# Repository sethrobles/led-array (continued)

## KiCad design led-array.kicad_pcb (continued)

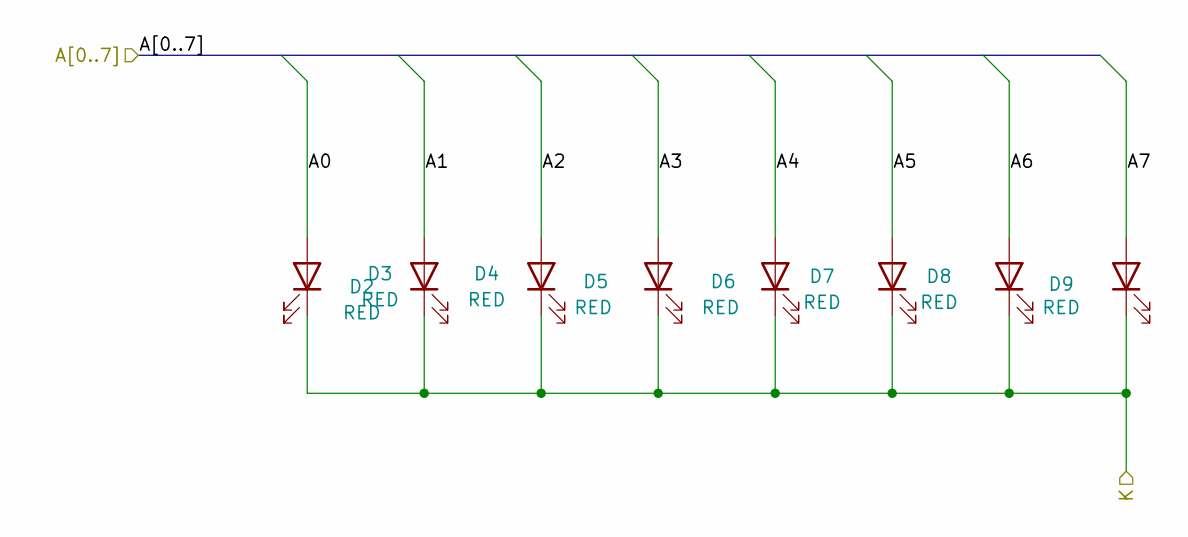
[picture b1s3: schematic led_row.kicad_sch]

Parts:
D2, D3, D4, D5, D6, D7, D8, D9: RED; LED_0603_1608Metric; LCSC C2286

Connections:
/LED Group 0/Led Module 1/A0: D2.2 (A); also elsewhere on the board
/LED Group 0/Led Module 1/A1: D3.2 (A); also elsewhere on the board
/LED Group 0/Led Module 1/A2: D4.2 (A); also elsewhere on the board
/LED Group 0/Led Module 1/A3: D5.2 (A); also elsewhere on the board
/LED Group 0/Led Module 1/A4: D6.2 (A); also elsewhere on the board
/LED Group 0/Led Module 1/A5: D7.2 (A); also elsewhere on the board
/LED Group 0/Led Module 1/A6: D8.2 (A); also elsewhere on the board
/LED Group 0/Led Module 1/A7: D9.2 (A); also elsewhere on the board
K5: D2.1 (K), D3.1 (K), D4.1 (K), D5.1 (K), D6.1 (K), D7.1 (K), D8.1 (K), D9.1 (K); also elsewhere on the board

Parts of its further copies:
D10, D11, D12, D13, D14, D15, D16, D17, D18, D19, D20, D21, D22, D23, D24, D25, D26, D27, D28, D29, D30, D31, D32, D33, D34, D35, D36, D37, D38, D39, D40, D41, D42, D43, D44, D45, D46, D47, D48, D49, D50, D51, D52, D53, D54, D55, D56, D57, D58, D59, D60, D61, D62, D63, D64, D65, D66, D67, D68, D69, D70, D71, D72, D73, D74, D75, D76, D77, D78, D79, D80, D81, D82, D83, D84, D85, D86, D87, D88, D89, D90, D91, D92, D93, D94, D95, D96, D97, D98, D99, D100, D101, D102, D103, D104, D105, D106, D107, D108, D109, D110, D111, D112, D113, D114, D115, D116, D117, D118, D119, D120, D121, D122, D123, D124, D125, D126, D127, D128, D129, D130, D131, D132, D133, D134, D135, D136, D137, D138, D139, D140, D141, D142, D143, D144, D145, D146, D147, D148, D149, D150, D151, D152, D153, D154, D155, D156, D157, D158, D159, D160, D161, D162, D163, D164, D165, D166, D167, D168, D169, D170, D171, D172, D173, D174, D175, D176, D177, D178, D179, D180, D181, D182, D183, D184, D185, D186, D187, D188, D189, D190, D191, D192, D193, D194, D195, D196, D197, D198, D199, D200, D201, D202, D203, D204, D205, D206, D207, D208, D209, D210, D211, D212, D213, D214, D215, D216, D217, D218, D219, D220, D221, D222, D223, D224, D225, D226, D227, D228, D229, D230, D231, D232, D233, D234, D235, D236, D237, D238, D239, D240, D241, D242, D243, D244, D245, D246, D247, D248, D249, D250, D251, D252, D253, D254, D255, D256, D257, D258, D259, D260, D261, D262, D263, D264, D265, D266, D267, D268, D269, D270, D271, D272, D273, D274, D275, D276, D277, D278, D279, D280, D281, D282, D283, D284, D285, D286, D287, D288, D289, D290, D291, D292, D293, D294, D295, D296, D297, D298, D299, D300, D301, D302, D303, D304, D305, D306, D307, D308, D309, D310, D311, D312, D313, D314, D315, D316, D317, D318, D319, D320, D321, D322, D323, D324, D325, D326, D327, D328, D329, D330, D331, D332, D333, D334, D335, D336, D337, D338, D339, D340, D341, D342, D343, D344, D345, D346, D347, D348, D349, D350, D351, D352, D353, D354, D355, D356, D357, D358, D359, D360, D361, D362, D363, D364, D365, D366, D367, D368, D369, D370, D371, D372, D373, D374, D375, D376, D377, D378, D379, D380, D381, D382, D383, D384, D385, D386, D387, D388, D389, D390, D391, D392, D393, D394, D395, D396, D397, D398, D399, D400, D401, D402, D403, D404, D405, D406, D407, D408, D409, D410, D411, D412, D413, D414, D415, D416, D417, D418, D419, D420, D421, D422, D423, D424, D425, D426, D427, D428, D429, D430, D431, D432, D433, D434, D435, D436, D437, D438, D439, D440, D441, D442, D443, D444, D445, D446, D447, D448, D449, D450, D451, D452, D453, D454, D455, D456, D457, D458, D459, D460, D461, D462, D463, D464, D465, D466, D467, D468, D469, D470, D471, D472, D473, D474, D475, D476, D477, D478, D479, D480, D481, D482, D483, D484, D485, D486, D487, D488, D489, D490, D491, D492, D493, D494, D495, D496, D497, D498, D499, D500, D501, D502, D503, D504, D505, D506, D507, D508, D509, D510, D511, D512, D513, D514, D515, D516, D517, D518, D519, D520, D521, D522, D523, D524, D525, D526, D527, D528, D529, D530, D531, D532, D533, D534, D535, D536, D537, D538, D539, D540, D541, D542, D543, D544, D545, D546, D547, D548, D549, D550, D551, D552, D553, D554, D555, D556, D557, D558, D559, D560, D561, D562, D563, D564, D565, D566, D567, D568, D569, D570, D571, D572, D573, D574, D575, D576, D577, D578, D579, D580, D581, D582, D583, D584, D585, D586, D587, D588, D589, D590, D591, D592, D593, D594, D595, D596, D597, D598, D599, D600, D601, D602, D603, D604, D605, D606, D607, D608, D609, D610, D611, D612, D613, D614, D615, D616, D617, D618, D619, D620, D621, D622, D623, D624, D625, D626, D627, D628, D629, D630, D631, D632, D633, D634, D635, D636, D637, D638, D639, D640, D641, D642, D643, D644, D645, D646, D647, D648, D649, D650, D651, D652, D653, D654, D655, D656, D657, D658, D659, D660, D661, D662, D663, D664, D665, D666, D667, D668, D669, D670, D671, D672, D673, D674, D675, D676, D677, D678, D679, D680, D681, D682, D683, D684, D685, D686, D687, D688, D689, D690, D691, D692, D693, D694, D695, D696, D697, D698, D699, D700, D701, D702, D703, D704, D705, D706, D707, D708, D709, D710, D711, D712, D713, D714, D715, D716, D717, D718, D719, D720, D721, D722, D723, D724, D725, D726, D727, D728, D729, D730, D731, D732, D733, D734, D735, D736, D737, D738, D739, D740, D741, D742, D743, D744, D745, D746, D747, D748, D749, D750, D751, D752, D753, D754, D755, D756, D757, D758, D759, D760, D761, D762, D763, D764, D765, D766, D767, D768, D769, D770, D771, D772, D773, D774, D775, D776, D777, D778, D779, D780, D781, D782, D783, D784, D785, D786, D787, D788, D789, D790, D791, D792, D793, D794, D795, D796, D797, D798, D799, D800, D801, D802, D803, D804, D805, D806, D807, D808, D809, D810, D811, D812, D813, D814, D815, D816, D817, D818, D819, D820, D821, D822, D823, D824, D825, D826, D827, D828, D829, D830, D831, D832, D833, D834, D835, D836, D837, D838, D839, D840, D841, D842, D843, D844, D845, D846, D847, D848, D849, D850, D851, D852, D853, D854, D855, D856, D857, D858, D859, D860, D861, D862, D863, D864, D865, D866, D867, D868, D869, D870, D871, D872, D873, D874, D875, D876, D877, D878, D879, D880, D881, D882, D883, D884, D885, D886, D887, D888, D889, D890, D891, D892, D893, D894, D895, D896, D897, D898, D899, D900, D901, D902, D903, D904, D905, D906, D907, D908, D909, D910, D911, D912, D913, D914, D915, D916, D917, D918, D919, D920, D921, D922, D923, D924, D925, D926, D927, D928, D929, D930, D931, D932, D933, D934, D935, D936, D937, D938, D939, D940, D941, D942, D943, D944, D945, D946, D947, D948, D949, D950, D951, D952, D953, D954, D955, D956, D957, D958, D959, D960, D961, D962, D963, D964, D965, D966, D967, D968, D969, D970, D971, D972, D973, D974, D975, D976, D977, D978, D979, D980, D981, D982, D983, D984, D985, D986, D987, D988, D989, D990, D991, D992, D993, D994, D995, D996, D997, D998, D999, D1000, D1001, D1002, D1003, D1004, D1005, D1006, D1007, D1008, D1009, D1010, D1011, D1012, D1013, D1014, D1015, D1016, D1017, D1018, D1019, D1020, D1021, D1022, D1023, D1024, D1025: RED; LED_0603_1608Metric; LCSC C2286

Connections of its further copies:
/LED Group 0/Led Module 1/A0: D10.2 (A), D18.2 (A), D26.2 (A), D34.2 (A), D42.2 (A), D50.2 (A), D58.2 (A); also elsewhere on the board
/LED Group 0/Led Module 1/A1: D11.2 (A), D19.2 (A), D27.2 (A), D35.2 (A), D43.2 (A), D51.2 (A), D59.2 (A); also elsewhere on the board
/LED Group 0/Led Module 1/A2: D12.2 (A), D20.2 (A), D28.2 (A), D36.2 (A), D44.2 (A), D52.2 (A), D60.2 (A); also elsewhere on the board
/LED Group 0/Led Module 1/A3: D13.2 (A), D21.2 (A), D29.2 (A), D37.2 (A), D45.2 (A), D53.2 (A), D61.2 (A); also elsewhere on the board
/LED Group 0/Led Module 1/A4: D14.2 (A), D22.2 (A), D30.2 (A), D38.2 (A), D46.2 (A), D54.2 (A), D62.2 (A); also elsewhere on the board
/LED Group 0/Led Module 1/A5: D15.2 (A), D23.2 (A), D31.2 (A), D39.2 (A), D47.2 (A), D55.2 (A), D63.2 (A); also elsewhere on the board
/LED Group 0/Led Module 1/A6: D16.2 (A), D24.2 (A), D32.2 (A), D40.2 (A), D48.2 (A), D56.2 (A), D64.2 (A); also elsewhere on the board
/LED Group 0/Led Module 1/A7: D17.2 (A), D25.2 (A), D33.2 (A), D41.2 (A), D49.2 (A), D57.2 (A), D65.2 (A); also elsewhere on the board
/LED Group 0/Led Module 2/A0: D66.2 (A), D74.2 (A), D82.2 (A), D90.2 (A), D98.2 (A), D106.2 (A), D114.2 (A), D122.2 (A); also elsewhere on the board
/LED Group 0/Led Module 2/A1: D67.2 (A), D75.2 (A), D83.2 (A), D91.2 (A), D99.2 (A), D107.2 (A), D115.2 (A), D123.2 (A); also elsewhere on the board
/LED Group 0/Led Module 2/A2: D68.2 (A), D76.2 (A), D84.2 (A), D92.2 (A), D100.2 (A), D108.2 (A), D116.2 (A), D124.2 (A); also elsewhere on the board
/LED Group 0/Led Module 2/A3: D69.2 (A), D77.2 (A), D85.2 (A), D93.2 (A), D101.2 (A), D109.2 (A), D117.2 (A), D125.2 (A); also elsewhere on the board
/LED Group 0/Led Module 2/A4: D70.2 (A), D78.2 (A), D86.2 (A), D94.2 (A), D102.2 (A), D110.2 (A), D118.2 (A), D126.2 (A); also elsewhere on the board
/LED Group 0/Led Module 2/A5: D71.2 (A), D79.2 (A), D87.2 (A), D95.2 (A), D103.2 (A), D111.2 (A), D119.2 (A), D127.2 (A); also elsewhere on the board
/LED Group 0/Led Module 2/A6: D72.2 (A), D80.2 (A), D88.2 (A), D96.2 (A), D104.2 (A), D112.2 (A), D120.2 (A), D128.2 (A); also elsewhere on the board
/LED Group 0/Led Module 2/A7: D73.2 (A), D81.2 (A), D89.2 (A), D97.2 (A), D105.2 (A), D113.2 (A), D121.2 (A), D129.2 (A); also elsewhere on the board
/LED Group 0/Led Module 3/A0: D130.2 (A), D138.2 (A), D146.2 (A), D154.2 (A), D162.2 (A), D170.2 (A), D218.2 (A), D226.2 (A); also elsewhere on the board
/LED Group 0/Led Module 3/A1: D131.2 (A), D139.2 (A), D147.2 (A), D155.2 (A), D163.2 (A), D171.2 (A), D219.2 (A), D227.2 (A); also elsewhere on the board
/LED Group 0/Led Module 3/A2: D132.2 (A), D140.2 (A), D148.2 (A), D156.2 (A), D164.2 (A), D172.2 (A), D220.2 (A), D228.2 (A); also elsewhere on the board
/LED Group 0/Led Module 3/A3: D133.2 (A), D141.2 (A), D149.2 (A), D157.2 (A), D165.2 (A), D173.2 (A), D221.2 (A), D229.2 (A); also elsewhere on the board
/LED Group 0/Led Module 3/A4: D134.2 (A), D142.2 (A), D150.2 (A), D158.2 (A), D166.2 (A), D174.2 (A), D222.2 (A), D230.2 (A); also elsewhere on the board
/LED Group 0/Led Module 3/A5: D135.2 (A), D143.2 (A), D151.2 (A), D159.2 (A), D167.2 (A), D175.2 (A), D223.2 (A), D231.2 (A); also elsewhere on the board
/LED Group 0/Led Module 3/A6: D136.2 (A), D144.2 (A), D152.2 (A), D160.2 (A), D168.2 (A), D176.2 (A), D224.2 (A), D232.2 (A); also elsewhere on the board
/LED Group 0/Led Module 3/A7: D137.2 (A), D145.2 (A), D153.2 (A), D161.2 (A), D169.2 (A), D177.2 (A), D225.2 (A), D233.2 (A); also elsewhere on the board
/LED Group 0/Led Module 4/A0: D274.2 (A), D282.2 (A), D338.2 (A), D346.2 (A), D394.2 (A), D402.2 (A), D450.2 (A), D458.2 (A); also elsewhere on the board
/LED Group 0/Led Module 4/A1: D275.2 (A), D283.2 (A), D339.2 (A), D347.2 (A), D395.2 (A), D403.2 (A), D451.2 (A), D459.2 (A); also elsewhere on the board
/LED Group 0/Led Module 4/A2: D276.2 (A), D284.2 (A), D340.2 (A), D348.2 (A), D396.2 (A), D404.2 (A), D452.2 (A), D460.2 (A); also elsewhere on the board
/LED Group 0/Led Module 4/A3: D277.2 (A), D285.2 (A), D341.2 (A), D349.2 (A), D397.2 (A), D405.2 (A), D453.2 (A), D461.2 (A); also elsewhere on the board
/LED Group 0/Led Module 4/A4: D278.2 (A), D286.2 (A), D342.2 (A), D350.2 (A), D398.2 (A), D406.2 (A), D454.2 (A), D462.2 (A); also elsewhere on the board
/LED Group 0/Led Module 4/A5: D279.2 (A), D287.2 (A), D343.2 (A), D351.2 (A), D399.2 (A), D407.2 (A), D455.2 (A), D463.2 (A); also elsewhere on the board
/LED Group 0/Led Module 4/A6: D280.2 (A), D288.2 (A), D344.2 (A), D352.2 (A), D400.2 (A), D408.2 (A), D456.2 (A), D464.2 (A); also elsewhere on the board
/LED Group 0/Led Module 4/A7: D281.2 (A), D289.2 (A), D345.2 (A), D353.2 (A), D401.2 (A), D409.2 (A), D457.2 (A), D465.2 (A); also elsewhere on the board
/LED Group 1/Led Module 1/A0: D258.2 (A), D266.2 (A), D290.2 (A), D298.2 (A), D306.2 (A), D314.2 (A), D322.2 (A), D330.2 (A); also elsewhere on the board
/LED Group 1/Led Module 1/A1: D259.2 (A), D267.2 (A), D291.2 (A), D299.2 (A), D307.2 (A), D315.2 (A), D323.2 (A), D331.2 (A); also elsewhere on the board
/LED Group 1/Led Module 1/A2: D260.2 (A), D268.2 (A), D292.2 (A), D300.2 (A), D308.2 (A), D316.2 (A), D324.2 (A), D332.2 (A); also elsewhere on the board
/LED Group 1/Led Module 1/A3: D261.2 (A), D269.2 (A), D293.2 (A), D301.2 (A), D309.2 (A), D317.2 (A), D325.2 (A), D333.2 (A); also elsewhere on the board
/LED Group 1/Led Module 1/A4: D262.2 (A), D270.2 (A), D294.2 (A), D302.2 (A), D310.2 (A), D318.2 (A), D326.2 (A), D334.2 (A); also elsewhere on the board
/LED Group 1/Led Module 1/A5: D263.2 (A), D271.2 (A), D295.2 (A), D303.2 (A), D311.2 (A), D319.2 (A), D327.2 (A), D335.2 (A); also elsewhere on the board
/LED Group 1/Led Module 1/A6: D264.2 (A), D272.2 (A), D296.2 (A), D304.2 (A), D312.2 (A), D320.2 (A), D328.2 (A), D336.2 (A); also elsewhere on the board
/LED Group 1/Led Module 1/A7: D265.2 (A), D273.2 (A), D297.2 (A), D305.2 (A), D313.2 (A), D321.2 (A), D329.2 (A), D337.2 (A); also elsewhere on the board
/LED Group 1/Led Module 2/A0: D178.2 (A), D186.2 (A), D194.2 (A), D202.2 (A), D210.2 (A), D234.2 (A), D242.2 (A), D250.2 (A); also elsewhere on the board
/LED Group 1/Led Module 2/A1: D179.2 (A), D187.2 (A), D195.2 (A), D203.2 (A), D211.2 (A), D235.2 (A), D243.2 (A), D251.2 (A); also elsewhere on the board
/LED Group 1/Led Module 2/A2: D180.2 (A), D188.2 (A), D196.2 (A), D204.2 (A), D212.2 (A), D236.2 (A), D244.2 (A), D252.2 (A); also elsewhere on the board
/LED Group 1/Led Module 2/A3: D181.2 (A), D189.2 (A), D197.2 (A), D205.2 (A), D213.2 (A), D237.2 (A), D245.2 (A), D253.2 (A); also elsewhere on the board
/LED Group 1/Led Module 2/A4: D182.2 (A), D190.2 (A), D198.2 (A), D206.2 (A), D214.2 (A), D238.2 (A), D246.2 (A), D254.2 (A); also elsewhere on the board
/LED Group 1/Led Module 2/A5: D183.2 (A), D191.2 (A), D199.2 (A), D207.2 (A), D215.2 (A), D239.2 (A), D247.2 (A), D255.2 (A); also elsewhere on the board
/LED Group 1/Led Module 2/A6: D184.2 (A), D192.2 (A), D200.2 (A), D208.2 (A), D216.2 (A), D240.2 (A), D248.2 (A), D256.2 (A); also elsewhere on the board
/LED Group 1/Led Module 2/A7: D185.2 (A), D193.2 (A), D201.2 (A), D209.2 (A), D217.2 (A), D241.2 (A), D249.2 (A), D257.2 (A); also elsewhere on the board
/LED Group 1/Led Module 3/A0: D354.2 (A), D362.2 (A), D370.2 (A), D378.2 (A), D386.2 (A), D410.2 (A), D418.2 (A), D426.2 (A); also elsewhere on the board
/LED Group 1/Led Module 3/A1: D355.2 (A), D363.2 (A), D371.2 (A), D379.2 (A), D387.2 (A), D411.2 (A), D419.2 (A), D427.2 (A); also elsewhere on the board
/LED Group 1/Led Module 3/A2: D356.2 (A), D364.2 (A), D372.2 (A), D380.2 (A), D388.2 (A), D412.2 (A), D420.2 (A), D428.2 (A); also elsewhere on the board
/LED Group 1/Led Module 3/A3: D357.2 (A), D365.2 (A), D373.2 (A), D381.2 (A), D389.2 (A), D413.2 (A), D421.2 (A), D429.2 (A); also elsewhere on the board
/LED Group 1/Led Module 3/A4: D358.2 (A), D366.2 (A), D374.2 (A), D382.2 (A), D390.2 (A), D414.2 (A), D422.2 (A), D430.2 (A); also elsewhere on the board
/LED Group 1/Led Module 3/A5: D359.2 (A), D367.2 (A), D375.2 (A), D383.2 (A), D391.2 (A), D415.2 (A), D423.2 (A), D431.2 (A); also elsewhere on the board
/LED Group 1/Led Module 3/A6: D360.2 (A), D368.2 (A), D376.2 (A), D384.2 (A), D392.2 (A), D416.2 (A), D424.2 (A), D432.2 (A); also elsewhere on the board
/LED Group 1/Led Module 3/A7: D361.2 (A), D369.2 (A), D377.2 (A), D385.2 (A), D393.2 (A), D417.2 (A), D425.2 (A), D433.2 (A); also elsewhere on the board
/LED Group 1/Led Module 4/A0: D434.2 (A), D442.2 (A), D466.2 (A), D474.2 (A), D482.2 (A), D490.2 (A), D498.2 (A), D506.2 (A); also elsewhere on the board
/LED Group 1/Led Module 4/A1: D435.2 (A), D443.2 (A), D467.2 (A), D475.2 (A), D483.2 (A), D491.2 (A), D499.2 (A), D507.2 (A); also elsewhere on the board
/LED Group 1/Led Module 4/A2: D436.2 (A), D444.2 (A), D468.2 (A), D476.2 (A), D484.2 (A), D492.2 (A), D500.2 (A), D508.2 (A); also elsewhere on the board
/LED Group 1/Led Module 4/A3: D437.2 (A), D445.2 (A), D469.2 (A), D477.2 (A), D485.2 (A), D493.2 (A), D501.2 (A), D509.2 (A); also elsewhere on the board
/LED Group 1/Led Module 4/A4: D438.2 (A), D446.2 (A), D470.2 (A), D478.2 (A), D486.2 (A), D494.2 (A), D502.2 (A), D510.2 (A); also elsewhere on the board
/LED Group 1/Led Module 4/A5: D439.2 (A), D447.2 (A), D471.2 (A), D479.2 (A), D487.2 (A), D495.2 (A), D503.2 (A), D511.2 (A); also elsewhere on the board
/LED Group 1/Led Module 4/A6: D440.2 (A), D448.2 (A), D472.2 (A), D480.2 (A), D488.2 (A), D496.2 (A), D504.2 (A), D512.2 (A); also elsewhere on the board
/LED Group 1/Led Module 4/A7: D441.2 (A), D449.2 (A), D473.2 (A), D481.2 (A), D489.2 (A), D497.2 (A), D505.2 (A), D513.2 (A); also elsewhere on the board
/LED Group 2/Led Module 1/A0: D578.2 (A), D586.2 (A), D594.2 (A), D602.2 (A), D610.2 (A), D618.2 (A), D626.2 (A), D634.2 (A); also elsewhere on the board
/LED Group 2/Led Module 1/A1: D579.2 (A), D587.2 (A), D595.2 (A), D603.2 (A), D611.2 (A), D619.2 (A), D627.2 (A), D635.2 (A); also elsewhere on the board
/LED Group 2/Led Module 1/A2: D580.2 (A), D588.2 (A), D596.2 (A), D604.2 (A), D612.2 (A), D620.2 (A), D628.2 (A), D636.2 (A); also elsewhere on the board
/LED Group 2/Led Module 1/A3: D581.2 (A), D589.2 (A), D597.2 (A), D605.2 (A), D613.2 (A), D621.2 (A), D629.2 (A), D637.2 (A); also elsewhere on the board
/LED Group 2/Led Module 1/A4: D582.2 (A), D590.2 (A), D598.2 (A), D606.2 (A), D614.2 (A), D622.2 (A), D630.2 (A), D638.2 (A); also elsewhere on the board
/LED Group 2/Led Module 1/A5: D583.2 (A), D591.2 (A), D599.2 (A), D607.2 (A), D615.2 (A), D623.2 (A), D631.2 (A), D639.2 (A); also elsewhere on the board
/LED Group 2/Led Module 1/A6: D584.2 (A), D592.2 (A), D600.2 (A), D608.2 (A), D616.2 (A), D624.2 (A), D632.2 (A), D640.2 (A); also elsewhere on the board
/LED Group 2/Led Module 1/A7: D585.2 (A), D593.2 (A), D601.2 (A), D609.2 (A), D617.2 (A), D625.2 (A), D633.2 (A), D641.2 (A); also elsewhere on the board
/LED Group 2/Led Module 2/A0: D514.2 (A), D522.2 (A), D530.2 (A), D538.2 (A), D546.2 (A), D554.2 (A), D562.2 (A), D570.2 (A); also elsewhere on the board
/LED Group 2/Led Module 2/A1: D515.2 (A), D523.2 (A), D531.2 (A), D539.2 (A), D547.2 (A), D555.2 (A), D563.2 (A), D571.2 (A); also elsewhere on the board
/LED Group 2/Led Module 2/A2: D516.2 (A), D524.2 (A), D532.2 (A), D540.2 (A), D548.2 (A), D556.2 (A), D564.2 (A), D572.2 (A); also elsewhere on the board
/LED Group 2/Led Module 2/A3: D517.2 (A), D525.2 (A), D533.2 (A), D541.2 (A), D549.2 (A), D557.2 (A), D565.2 (A), D573.2 (A); also elsewhere on the board
/LED Group 2/Led Module 2/A4: D518.2 (A), D526.2 (A), D534.2 (A), D542.2 (A), D550.2 (A), D558.2 (A), D566.2 (A), D574.2 (A); also elsewhere on the board
/LED Group 2/Led Module 2/A5: D519.2 (A), D527.2 (A), D535.2 (A), D543.2 (A), D551.2 (A), D559.2 (A), D567.2 (A), D575.2 (A); also elsewhere on the board
/LED Group 2/Led Module 2/A6: D520.2 (A), D528.2 (A), D536.2 (A), D544.2 (A), D552.2 (A), D560.2 (A), D568.2 (A), D576.2 (A); also elsewhere on the board
/LED Group 2/Led Module 2/A7: D521.2 (A), D529.2 (A), D537.2 (A), D545.2 (A), D553.2 (A), D561.2 (A), D569.2 (A), D577.2 (A); also elsewhere on the board
/LED Group 2/Led Module 3/A0: D642.2 (A), D650.2 (A), D658.2 (A), D666.2 (A), D674.2 (A), D682.2 (A), D690.2 (A), D698.2 (A); also elsewhere on the board
/LED Group 2/Led Module 3/A1: D643.2 (A), D651.2 (A), D659.2 (A), D667.2 (A), D675.2 (A), D683.2 (A), D691.2 (A), D699.2 (A); also elsewhere on the board
/LED Group 2/Led Module 3/A2: D644.2 (A), D652.2 (A), D660.2 (A), D668.2 (A), D676.2 (A), D684.2 (A), D692.2 (A), D700.2 (A); also elsewhere on the board
/LED Group 2/Led Module 3/A3: D645.2 (A), D653.2 (A), D661.2 (A), D669.2 (A), D677.2 (A), D685.2 (A), D693.2 (A), D701.2 (A); also elsewhere on the board
/LED Group 2/Led Module 3/A4: D646.2 (A), D654.2 (A), D662.2 (A), D670.2 (A), D678.2 (A), D686.2 (A), D694.2 (A), D702.2 (A); also elsewhere on the board
/LED Group 2/Led Module 3/A5: D647.2 (A), D655.2 (A), D663.2 (A), D671.2 (A), D679.2 (A), D687.2 (A), D695.2 (A), D703.2 (A); also elsewhere on the board
/LED Group 2/Led Module 3/A6: D648.2 (A), D656.2 (A), D664.2 (A), D672.2 (A), D680.2 (A), D688.2 (A), D696.2 (A), D704.2 (A); also elsewhere on the board
/LED Group 2/Led Module 3/A7: D649.2 (A), D657.2 (A), D665.2 (A), D673.2 (A), D681.2 (A), D689.2 (A), D697.2 (A), D705.2 (A); also elsewhere on the board
/LED Group 2/Led Module 4/A0: D706.2 (A), D714.2 (A), D722.2 (A), D730.2 (A), D738.2 (A), D746.2 (A), D754.2 (A), D762.2 (A); also elsewhere on the board
/LED Group 2/Led Module 4/A1: D707.2 (A), D715.2 (A), D723.2 (A), D731.2 (A), D739.2 (A), D747.2 (A), D755.2 (A), D763.2 (A); also elsewhere on the board
/LED Group 2/Led Module 4/A2: D708.2 (A), D716.2 (A), D724.2 (A), D732.2 (A), D740.2 (A), D748.2 (A), D756.2 (A), D764.2 (A); also elsewhere on the board
/LED Group 2/Led Module 4/A3: D709.2 (A), D717.2 (A), D725.2 (A), D733.2 (A), D741.2 (A), D749.2 (A), D757.2 (A), D765.2 (A); also elsewhere on the board
/LED Group 2/Led Module 4/A4: D710.2 (A), D718.2 (A), D726.2 (A), D734.2 (A), D742.2 (A), D750.2 (A), D758.2 (A), D766.2 (A); also elsewhere on the board
/LED Group 2/Led Module 4/A5: D711.2 (A), D719.2 (A), D727.2 (A), D735.2 (A), D743.2 (A), D751.2 (A), D759.2 (A), D767.2 (A); also elsewhere on the board
/LED Group 2/Led Module 4/A6: D712.2 (A), D720.2 (A), D728.2 (A), D736.2 (A), D744.2 (A), D752.2 (A), D760.2 (A), D768.2 (A); also elsewhere on the board
/LED Group 2/Led Module 4/A7: D713.2 (A), D721.2 (A), D729.2 (A), D737.2 (A), D745.2 (A), D753.2 (A), D761.2 (A), D769.2 (A); also elsewhere on the board
/LED Group 3/Led Module 1/A0: D834.2 (A), D842.2 (A), D850.2 (A), D858.2 (A), D866.2 (A), D874.2 (A), D882.2 (A), D890.2 (A); also elsewhere on the board
/LED Group 3/Led Module 1/A1: D835.2 (A), D843.2 (A), D851.2 (A), D859.2 (A), D867.2 (A), D875.2 (A), D883.2 (A), D891.2 (A); also elsewhere on the board
/LED Group 3/Led Module 1/A2: D836.2 (A), D844.2 (A), D852.2 (A), D860.2 (A), D868.2 (A), D876.2 (A), D884.2 (A), D892.2 (A); also elsewhere on the board
/LED Group 3/Led Module 1/A3: D837.2 (A), D845.2 (A), D853.2 (A), D861.2 (A), D869.2 (A), D877.2 (A), D885.2 (A), D893.2 (A); also elsewhere on the board
/LED Group 3/Led Module 1/A4: D838.2 (A), D846.2 (A), D854.2 (A), D862.2 (A), D870.2 (A), D878.2 (A), D886.2 (A), D894.2 (A); also elsewhere on the board
/LED Group 3/Led Module 1/A5: D839.2 (A), D847.2 (A), D855.2 (A), D863.2 (A), D871.2 (A), D879.2 (A), D887.2 (A), D895.2 (A); also elsewhere on the board
/LED Group 3/Led Module 1/A6: D840.2 (A), D848.2 (A), D856.2 (A), D864.2 (A), D872.2 (A), D880.2 (A), D888.2 (A), D896.2 (A); also elsewhere on the board
/LED Group 3/Led Module 1/A7: D841.2 (A), D849.2 (A), D857.2 (A), D865.2 (A), D873.2 (A), D881.2 (A), D889.2 (A), D897.2 (A); also elsewhere on the board
/LED Group 3/Led Module 2/A0: D770.2 (A), D778.2 (A), D786.2 (A), D794.2 (A), D802.2 (A), D810.2 (A), D818.2 (A), D826.2 (A); also elsewhere on the board
/LED Group 3/Led Module 2/A1: D771.2 (A), D779.2 (A), D787.2 (A), D795.2 (A), D803.2 (A), D811.2 (A), D819.2 (A), D827.2 (A); also elsewhere on the board
/LED Group 3/Led Module 2/A2: D772.2 (A), D780.2 (A), D788.2 (A), D796.2 (A), D804.2 (A), D812.2 (A), D820.2 (A), D828.2 (A); also elsewhere on the board
/LED Group 3/Led Module 2/A3: D773.2 (A), D781.2 (A), D789.2 (A), D797.2 (A), D805.2 (A), D813.2 (A), D821.2 (A), D829.2 (A); also elsewhere on the board
/LED Group 3/Led Module 2/A4: D774.2 (A), D782.2 (A), D790.2 (A), D798.2 (A), D806.2 (A), D814.2 (A), D822.2 (A), D830.2 (A); also elsewhere on the board
/LED Group 3/Led Module 2/A5: D775.2 (A), D783.2 (A), D791.2 (A), D799.2 (A), D807.2 (A), D815.2 (A), D823.2 (A), D831.2 (A); also elsewhere on the board
/LED Group 3/Led Module 2/A6: D776.2 (A), D784.2 (A), D792.2 (A), D800.2 (A), D808.2 (A), D816.2 (A), D824.2 (A), D832.2 (A); also elsewhere on the board
/LED Group 3/Led Module 2/A7: D777.2 (A), D785.2 (A), D793.2 (A), D801.2 (A), D809.2 (A), D817.2 (A), D825.2 (A), D833.2 (A); also elsewhere on the board
/LED Group 3/Led Module 3/A0: D898.2 (A), D906.2 (A), D914.2 (A), D922.2 (A), D930.2 (A), D938.2 (A), D946.2 (A), D954.2 (A); also elsewhere on the board
/LED Group 3/Led Module 3/A1: D899.2 (A), D907.2 (A), D915.2 (A), D923.2 (A), D931.2 (A), D939.2 (A), D947.2 (A), D955.2 (A); also elsewhere on the board
/LED Group 3/Led Module 3/A2: D900.2 (A), D908.2 (A), D916.2 (A), D924.2 (A), D932.2 (A), D940.2 (A), D948.2 (A), D956.2 (A); also elsewhere on the board
/LED Group 3/Led Module 3/A3: D901.2 (A), D909.2 (A), D917.2 (A), D925.2 (A), D933.2 (A), D941.2 (A), D949.2 (A), D957.2 (A); also elsewhere on the board
/LED Group 3/Led Module 3/A4: D902.2 (A), D910.2 (A), D918.2 (A), D926.2 (A), D934.2 (A), D942.2 (A), D950.2 (A), D958.2 (A); also elsewhere on the board
/LED Group 3/Led Module 3/A5: D903.2 (A), D911.2 (A), D919.2 (A), D927.2 (A), D935.2 (A), D943.2 (A), D951.2 (A), D959.2 (A); also elsewhere on the board
/LED Group 3/Led Module 3/A6: D904.2 (A), D912.2 (A), D920.2 (A), D928.2 (A), D936.2 (A), D944.2 (A), D952.2 (A), D960.2 (A); also elsewhere on the board
/LED Group 3/Led Module 3/A7: D905.2 (A), D913.2 (A), D921.2 (A), D929.2 (A), D937.2 (A), D945.2 (A), D953.2 (A), D961.2 (A); also elsewhere on the board
/LED Group 3/Led Module 4/A0: D962.2 (A), D970.2 (A), D978.2 (A), D986.2 (A), D994.2 (A), D1002.2 (A), D1010.2 (A), D1018.2 (A); also elsewhere on the board
/LED Group 3/Led Module 4/A1: D963.2 (A), D971.2 (A), D979.2 (A), D987.2 (A), D995.2 (A), D1003.2 (A), D1011.2 (A), D1019.2 (A); also elsewhere on the board
/LED Group 3/Led Module 4/A2: D964.2 (A), D972.2 (A), D980.2 (A), D988.2 (A), D996.2 (A), D1004.2 (A), D1012.2 (A), D1020.2 (A); also elsewhere on the board
/LED Group 3/Led Module 4/A3: D965.2 (A), D973.2 (A), D981.2 (A), D989.2 (A), D997.2 (A), D1005.2 (A), D1013.2 (A), D1021.2 (A); also elsewhere on the board
/LED Group 3/Led Module 4/A4: D966.2 (A), D974.2 (A), D982.2 (A), D990.2 (A), D998.2 (A), D1006.2 (A), D1014.2 (A), D1022.2 (A); also elsewhere on the board
/LED Group 3/Led Module 4/A5: D967.2 (A), D975.2 (A), D983.2 (A), D991.2 (A), D999.2 (A), D1007.2 (A), D1015.2 (A), D1023.2 (A); also elsewhere on the board
/LED Group 3/Led Module 4/A6: D968.2 (A), D976.2 (A), D984.2 (A), D992.2 (A), D1000.2 (A), D1008.2 (A), D1016.2 (A), D1024.2 (A); also elsewhere on the board
/LED Group 3/Led Module 4/A7: D969.2 (A), D977.2 (A), D985.2 (A), D993.2 (A), D1001.2 (A), D1009.2 (A), D1017.2 (A), D1025.2 (A); also elsewhere on the board
K0: D26.1 (K), D27.1 (K), D28.1 (K), D29.1 (K), D30.1 (K), D31.1 (K), D32.1 (K), D33.1 (K), D90.1 (K), D91.1 (K), D92.1 (K), D93.1 (K), D94.1 (K), D95.1 (K), D96.1 (K), D97.1 (K), D154.1 (K), D155.1 (K), D156.1 (K), D157.1 (K), D158.1 (K), D159.1 (K), D160.1 (K), D161.1 (K), D202.1 (K), D203.1 (K), D204.1 (K), D205.1 (K), D206.1 (K), D207.1 (K), D208.1 (K), D209.1 (K), D298.1 (K), D299.1 (K), D300.1 (K), D301.1 (K), D302.1 (K), D303.1 (K), D304.1 (K), D305.1 (K), D346.1 (K), D347.1 (K), D348.1 (K), D349.1 (K), D350.1 (K), D351.1 (K), D352.1 (K), D353.1 (K), D378.1 (K), D379.1 (K), D380.1 (K), D381.1 (K), D382.1 (K), D383.1 (K), D384.1 (K), D385.1 (K), D474.1 (K), D475.1 (K), D476.1 (K), D477.1 (K), D478.1 (K), D479.1 (K), D480.1 (K), D481.1 (K), D538.1 (K), D539.1 (K), D540.1 (K), D541.1 (K), D542.1 (K), D543.1 (K), D544.1 (K), D545.1 (K), D602.1 (K), D603.1 (K), D604.1 (K), D605.1 (K), D606.1 (K), D607.1 (K), D608.1 (K), D609.1 (K), D666.1 (K), D667.1 (K), D668.1 (K), D669.1 (K), D670.1 (K), D671.1 (K), D672.1 (K), D673.1 (K), D730.1 (K), D731.1 (K), D732.1 (K), D733.1 (K), D734.1 (K), D735.1 (K), D736.1 (K), D737.1 (K), D794.1 (K), D795.1 (K), D796.1 (K), D797.1 (K), D798.1 (K), D799.1 (K), D800.1 (K), D801.1 (K), D858.1 (K), D859.1 (K), D860.1 (K), D861.1 (K), D862.1 (K), D863.1 (K), D864.1 (K), D865.1 (K), D922.1 (K), D923.1 (K), D924.1 (K), D925.1 (K), D926.1 (K), D927.1 (K), D928.1 (K), D929.1 (K), D986.1 (K), D987.1 (K), D988.1 (K), D989.1 (K), D990.1 (K), D991.1 (K), D992.1 (K), D993.1 (K); also elsewhere on the board
K1: D34.1 (K), D35.1 (K), D36.1 (K), D37.1 (K), D38.1 (K), D39.1 (K), D40.1 (K), D41.1 (K), D98.1 (K), D99.1 (K), D100.1 (K), D101.1 (K), D102.1 (K), D103.1 (K), D104.1 (K), D105.1 (K), D162.1 (K), D163.1 (K), D164.1 (K), D165.1 (K), D166.1 (K), D167.1 (K), D168.1 (K), D169.1 (K), D210.1 (K), D211.1 (K), D212.1 (K), D213.1 (K), D214.1 (K), D215.1 (K), D216.1 (K), D217.1 (K), D306.1 (K), D307.1 (K), D308.1 (K), D309.1 (K), D310.1 (K), D311.1 (K), D312.1 (K), D313.1 (K), D386.1 (K), D387.1 (K), D388.1 (K), D389.1 (K), D390.1 (K), D391.1 (K), D392.1 (K), D393.1 (K), D394.1 (K), D395.1 (K), D396.1 (K), D397.1 (K), D398.1 (K), D399.1 (K), D400.1 (K), D401.1 (K), D482.1 (K), D483.1 (K), D484.1 (K), D485.1 (K), D486.1 (K), D487.1 (K), D488.1 (K), D489.1 (K), D546.1 (K), D547.1 (K), D548.1 (K), D549.1 (K), D550.1 (K), D551.1 (K), D552.1 (K), D553.1 (K), D610.1 (K), D611.1 (K), D612.1 (K), D613.1 (K), D614.1 (K), D615.1 (K), D616.1 (K), D617.1 (K), D674.1 (K), D675.1 (K), D676.1 (K), D677.1 (K), D678.1 (K), D679.1 (K), D680.1 (K), D681.1 (K), D738.1 (K), D739.1 (K), D740.1 (K), D741.1 (K), D742.1 (K), D743.1 (K), D744.1 (K), D745.1 (K), D802.1 (K), D803.1 (K), D804.1 (K), D805.1 (K), D806.1 (K), D807.1 (K), D808.1 (K), D809.1 (K), D866.1 (K), D867.1 (K), D868.1 (K), D869.1 (K), D870.1 (K), D871.1 (K), D872.1 (K), D873.1 (K), D930.1 (K), D931.1 (K), D932.1 (K), D933.1 (K), D934.1 (K), D935.1 (K), D936.1 (K), D937.1 (K), D994.1 (K), D995.1 (K), D996.1 (K), D997.1 (K), D998.1 (K), D999.1 (K), D1000.1 (K), D1001.1 (K); also elsewhere on the board
K2: D58.1 (K), D59.1 (K), D60.1 (K), D61.1 (K), D62.1 (K), D63.1 (K), D64.1 (K), D65.1 (K), D122.1 (K), D123.1 (K), D124.1 (K), D125.1 (K), D126.1 (K), D127.1 (K), D128.1 (K), D129.1 (K), D226.1 (K), D227.1 (K), D228.1 (K), D229.1 (K), D230.1 (K), D231.1 (K), D232.1 (K), D233.1 (K), D250.1 (K), D251.1 (K), D252.1 (K), D253.1 (K), D254.1 (K), D255.1 (K), D256.1 (K), D257.1 (K), D330.1 (K), D331.1 (K), D332.1 (K), D333.1 (K), D334.1 (K), D335.1 (K), D336.1 (K), D337.1 (K), D426.1 (K), D427.1 (K), D428.1 (K), D429.1 (K), D430.1 (K), D431.1 (K), D432.1 (K), D433.1 (K), D458.1 (K), D459.1 (K), D460.1 (K), D461.1 (K), D462.1 (K), D463.1 (K), D464.1 (K), D465.1 (K), D506.1 (K), D507.1 (K), D508.1 (K), D509.1 (K), D510.1 (K), D511.1 (K), D512.1 (K), D513.1 (K), D570.1 (K), D571.1 (K), D572.1 (K), D573.1 (K), D574.1 (K), D575.1 (K), D576.1 (K), D577.1 (K), D634.1 (K), D635.1 (K), D636.1 (K), D637.1 (K), D638.1 (K), D639.1 (K), D640.1 (K), D641.1 (K), D698.1 (K), D699.1 (K), D700.1 (K), D701.1 (K), D702.1 (K), D703.1 (K), D704.1 (K), D705.1 (K), D762.1 (K), D763.1 (K), D764.1 (K), D765.1 (K), D766.1 (K), D767.1 (K), D768.1 (K), D769.1 (K), D826.1 (K), D827.1 (K), D828.1 (K), D829.1 (K), D830.1 (K), D831.1 (K), D832.1 (K), D833.1 (K), D890.1 (K), D891.1 (K), D892.1 (K), D893.1 (K), D894.1 (K), D895.1 (K), D896.1 (K), D897.1 (K), D954.1 (K), D955.1 (K), D956.1 (K), D957.1 (K), D958.1 (K), D959.1 (K), D960.1 (K), D961.1 (K), D1018.1 (K), D1019.1 (K), D1020.1 (K), D1021.1 (K), D1022.1 (K), D1023.1 (K), D1024.1 (K), D1025.1 (K); also elsewhere on the board
K3: D50.1 (K), D51.1 (K), D52.1 (K), D53.1 (K), D54.1 (K), D55.1 (K), D56.1 (K), D57.1 (K), D114.1 (K), D115.1 (K), D116.1 (K), D117.1 (K), D118.1 (K), D119.1 (K), D120.1 (K), D121.1 (K), D218.1 (K), D219.1 (K), D220.1 (K), D221.1 (K), D222.1 (K), D223.1 (K), D224.1 (K), D225.1 (K), D242.1 (K), D243.1 (K), D244.1 (K), D245.1 (K), D246.1 (K), D247.1 (K), D248.1 (K), D249.1 (K), D322.1 (K), D323.1 (K), D324.1 (K), D325.1 (K), D326.1 (K), D327.1 (K), D328.1 (K), D329.1 (K), D418.1 (K), D419.1 (K), D420.1 (K), D421.1 (K), D422.1 (K), D423.1 (K), D424.1 (K), D425.1 (K), D450.1 (K), D451.1 (K), D452.1 (K), D453.1 (K), D454.1 (K), D455.1 (K), D456.1 (K), D457.1 (K), D498.1 (K), D499.1 (K), D500.1 (K), D501.1 (K), D502.1 (K), D503.1 (K), D504.1 (K), D505.1 (K), D562.1 (K), D563.1 (K), D564.1 (K), D565.1 (K), D566.1 (K), D567.1 (K), D568.1 (K), D569.1 (K), D626.1 (K), D627.1 (K), D628.1 (K), D629.1 (K), D630.1 (K), D631.1 (K), D632.1 (K), D633.1 (K), D690.1 (K), D691.1 (K), D692.1 (K), D693.1 (K), D694.1 (K), D695.1 (K), D696.1 (K), D697.1 (K), D754.1 (K), D755.1 (K), D756.1 (K), D757.1 (K), D758.1 (K), D759.1 (K), D760.1 (K), D761.1 (K), D818.1 (K), D819.1 (K), D820.1 (K), D821.1 (K), D822.1 (K), D823.1 (K), D824.1 (K), D825.1 (K), D882.1 (K), D883.1 (K), D884.1 (K), D885.1 (K), D886.1 (K), D887.1 (K), D888.1 (K), D889.1 (K), D946.1 (K), D947.1 (K), D948.1 (K), D949.1 (K), D950.1 (K), D951.1 (K), D952.1 (K), D953.1 (K), D1010.1 (K), D1011.1 (K), D1012.1 (K), D1013.1 (K), D1014.1 (K), D1015.1 (K), D1016.1 (K), D1017.1 (K); also elsewhere on the board
K4: D42.1 (K), D43.1 (K), D44.1 (K), D45.1 (K), D46.1 (K), D47.1 (K), D48.1 (K), D49.1 (K), D106.1 (K), D107.1 (K), D108.1 (K), D109.1 (K), D110.1 (K), D111.1 (K), D112.1 (K), D113.1 (K), D170.1 (K), D171.1 (K), D172.1 (K), D173.1 (K), D174.1 (K), D175.1 (K), D176.1 (K), D177.1 (K), D234.1 (K), D235.1 (K), D236.1 (K), D237.1 (K), D238.1 (K), D239.1 (K), D240.1 (K), D241.1 (K), D314.1 (K), D315.1 (K), D316.1 (K), D317.1 (K), D318.1 (K), D319.1 (K), D320.1 (K), D321.1 (K), D402.1 (K), D403.1 (K), D404.1 (K), D405.1 (K), D406.1 (K), D407.1 (K), D408.1 (K), D409.1 (K), D410.1 (K), D411.1 (K), D412.1 (K), D413.1 (K), D414.1 (K), D415.1 (K), D416.1 (K), D417.1 (K), D490.1 (K), D491.1 (K), D492.1 (K), D493.1 (K), D494.1 (K), D495.1 (K), D496.1 (K), D497.1 (K), D554.1 (K), D555.1 (K), D556.1 (K), D557.1 (K), D558.1 (K), D559.1 (K), D560.1 (K), D561.1 (K), D618.1 (K), D619.1 (K), D620.1 (K), D621.1 (K), D622.1 (K), D623.1 (K), D624.1 (K), D625.1 (K), D682.1 (K), D683.1 (K), D684.1 (K), D685.1 (K), D686.1 (K), D687.1 (K), D688.1 (K), D689.1 (K), D746.1 (K), D747.1 (K), D748.1 (K), D749.1 (K), D750.1 (K), D751.1 (K), D752.1 (K), D753.1 (K), D810.1 (K), D811.1 (K), D812.1 (K), D813.1 (K), D814.1 (K), D815.1 (K), D816.1 (K), D817.1 (K), D874.1 (K), D875.1 (K), D876.1 (K), D877.1 (K), D878.1 (K), D879.1 (K), D880.1 (K), D881.1 (K), D938.1 (K), D939.1 (K), D940.1 (K), D941.1 (K), D942.1 (K), D943.1 (K), D944.1 (K), D945.1 (K), D1002.1 (K), D1003.1 (K), D1004.1 (K), D1005.1 (K), D1006.1 (K), D1007.1 (K), D1008.1 (K), D1009.1 (K); also elsewhere on the board
K5: D66.1 (K), D67.1 (K), D68.1 (K), D69.1 (K), D70.1 (K), D71.1 (K), D72.1 (K), D73.1 (K), D130.1 (K), D131.1 (K), D132.1 (K), D133.1 (K), D134.1 (K), D135.1 (K), D136.1 (K), D137.1 (K), D178.1 (K), D179.1 (K), D180.1 (K), D181.1 (K), D182.1 (K), D183.1 (K), D184.1 (K), D185.1 (K), D258.1 (K), D259.1 (K), D260.1 (K), D261.1 (K), D262.1 (K), D263.1 (K), D264.1 (K), D265.1 (K), D274.1 (K), D275.1 (K), D276.1 (K), D277.1 (K), D278.1 (K), D279.1 (K), D280.1 (K), D281.1 (K), D354.1 (K), D355.1 (K), D356.1 (K), D357.1 (K), D358.1 (K), D359.1 (K), D360.1 (K), D361.1 (K), D434.1 (K), D435.1 (K), D436.1 (K), D437.1 (K), D438.1 (K), D439.1 (K), D440.1 (K), D441.1 (K), D514.1 (K), D515.1 (K), D516.1 (K), D517.1 (K), D518.1 (K), D519.1 (K), D520.1 (K), D521.1 (K), D578.1 (K), D579.1 (K), D580.1 (K), D581.1 (K), D582.1 (K), D583.1 (K), D584.1 (K), D585.1 (K), D642.1 (K), D643.1 (K), D644.1 (K), D645.1 (K), D646.1 (K), D647.1 (K), D648.1 (K), D649.1 (K), D706.1 (K), D707.1 (K), D708.1 (K), D709.1 (K), D710.1 (K), D711.1 (K), D712.1 (K), D713.1 (K), D770.1 (K), D771.1 (K), D772.1 (K), D773.1 (K), D774.1 (K), D775.1 (K), D776.1 (K), D777.1 (K), D834.1 (K), D835.1 (K), D836.1 (K), D837.1 (K), D838.1 (K), D839.1 (K), D840.1 (K), D841.1 (K), D898.1 (K), D899.1 (K), D900.1 (K), D901.1 (K), D902.1 (K), D903.1 (K), D904.1 (K), D905.1 (K), D962.1 (K), D963.1 (K), D964.1 (K), D965.1 (K), D966.1 (K), D967.1 (K), D968.1 (K), D969.1 (K); also elsewhere on the board
K6: D18.1 (K), D19.1 (K), D20.1 (K), D21.1 (K), D22.1 (K), D23.1 (K), D24.1 (K), D25.1 (K), D82.1 (K), D83.1 (K), D84.1 (K), D85.1 (K), D86.1 (K), D87.1 (K), D88.1 (K), D89.1 (K), D146.1 (K), D147.1 (K), D148.1 (K), D149.1 (K), D150.1 (K), D151.1 (K), D152.1 (K), D153.1 (K), D194.1 (K), D195.1 (K), D196.1 (K), D197.1 (K), D198.1 (K), D199.1 (K), D200.1 (K), D201.1 (K), D290.1 (K), D291.1 (K), D292.1 (K), D293.1 (K), D294.1 (K), D295.1 (K), D296.1 (K), D297.1 (K), D338.1 (K), D339.1 (K), D340.1 (K), D341.1 (K), D342.1 (K), D343.1 (K), D344.1 (K), D345.1 (K), D370.1 (K), D371.1 (K), D372.1 (K), D373.1 (K), D374.1 (K), D375.1 (K), D376.1 (K), D377.1 (K), D466.1 (K), D467.1 (K), D468.1 (K), D469.1 (K), D470.1 (K), D471.1 (K), D472.1 (K), D473.1 (K), D530.1 (K), D531.1 (K), D532.1 (K), D533.1 (K), D534.1 (K), D535.1 (K), D536.1 (K), D537.1 (K), D594.1 (K), D595.1 (K), D596.1 (K), D597.1 (K), D598.1 (K), D599.1 (K), D600.1 (K), D601.1 (K), D658.1 (K), D659.1 (K), D660.1 (K), D661.1 (K), D662.1 (K), D663.1 (K), D664.1 (K), D665.1 (K), D722.1 (K), D723.1 (K), D724.1 (K), D725.1 (K), D726.1 (K), D727.1 (K), D728.1 (K), D729.1 (K), D786.1 (K), D787.1 (K), D788.1 (K), D789.1 (K), D790.1 (K), D791.1 (K), D792.1 (K), D793.1 (K), D850.1 (K), D851.1 (K), D852.1 (K), D853.1 (K), D854.1 (K), D855.1 (K), D856.1 (K), D857.1 (K), D914.1 (K), D915.1 (K), D916.1 (K), D917.1 (K), D918.1 (K), D919.1 (K), D920.1 (K), D921.1 (K), D978.1 (K), D979.1 (K), D980.1 (K), D981.1 (K), D982.1 (K), D983.1 (K), D984.1 (K), D985.1 (K); also elsewhere on the board
K7: D10.1 (K), D11.1 (K), D12.1 (K), D13.1 (K), D14.1 (K), D15.1 (K), D16.1 (K), D17.1 (K), D74.1 (K), D75.1 (K), D76.1 (K), D77.1 (K), D78.1 (K), D79.1 (K), D80.1 (K), D81.1 (K), D138.1 (K), D139.1 (K), D140.1 (K), D141.1 (K), D142.1 (K), D143.1 (K), D144.1 (K), D145.1 (K), D186.1 (K), D187.1 (K), D188.1 (K), D189.1 (K), D190.1 (K), D191.1 (K), D192.1 (K), D193.1 (K), D266.1 (K), D267.1 (K), D268.1 (K), D269.1 (K), D270.1 (K), D271.1 (K), D272.1 (K), D273.1 (K), D282.1 (K), D283.1 (K), D284.1 (K), D285.1 (K), D286.1 (K), D287.1 (K), D288.1 (K), D289.1 (K), D362.1 (K), D363.1 (K), D364.1 (K), D365.1 (K), D366.1 (K), D367.1 (K), D368.1 (K), D369.1 (K), D442.1 (K), D443.1 (K), D444.1 (K), D445.1 (K), D446.1 (K), D447.1 (K), D448.1 (K), D449.1 (K), D522.1 (K), D523.1 (K), D524.1 (K), D525.1 (K), D526.1 (K), D527.1 (K), D528.1 (K), D529.1 (K), D586.1 (K), D587.1 (K), D588.1 (K), D589.1 (K), D590.1 (K), D591.1 (K), D592.1 (K), D593.1 (K), D650.1 (K), D651.1 (K), D652.1 (K), D653.1 (K), D654.1 (K), D655.1 (K), D656.1 (K), D657.1 (K), D714.1 (K), D715.1 (K), D716.1 (K), D717.1 (K), D718.1 (K), D719.1 (K), D720.1 (K), D721.1 (K), D778.1 (K), D779.1 (K), D780.1 (K), D781.1 (K), D782.1 (K), D783.1 (K), D784.1 (K), D785.1 (K), D842.1 (K), D843.1 (K), D844.1 (K), D845.1 (K), D846.1 (K), D847.1 (K), D848.1 (K), D849.1 (K), D906.1 (K), D907.1 (K), D908.1 (K), D909.1 (K), D910.1 (K), D911.1 (K), D912.1 (K), D913.1 (K), D970.1 (K), D971.1 (K), D972.1 (K), D973.1 (K), D974.1 (K), D975.1 (K), D976.1 (K), D977.1 (K); also elsewhere on the board
